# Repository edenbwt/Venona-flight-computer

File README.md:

# Venona flight computer
the goal of this flight computer is to be easy to manufacture be mobulable for all kind of mission 

## Goal

- log fly data
- 4 pyro chanel
- quite light
- Arduino C++ firmware

## Parts
- Teensy 3.6 dev board
- mpu6050
- bosch bmp280
- n chanel mosfet for pyro
- tricolor Led
- buzzer

## The rocket

- this is the rocket the computer will be tested on 
- this rocket is design on [Open Rocket](https://openrocket.info/)

## The board

- this is the board, i made it in one 10h go i probably fuck it up doing it BUT i think it will run for testing for now
- i will by all the part after christmas so i can try it out later in 2023
- this board is design on [Autodesk Eagle](http://eagle.autodesk.com/)

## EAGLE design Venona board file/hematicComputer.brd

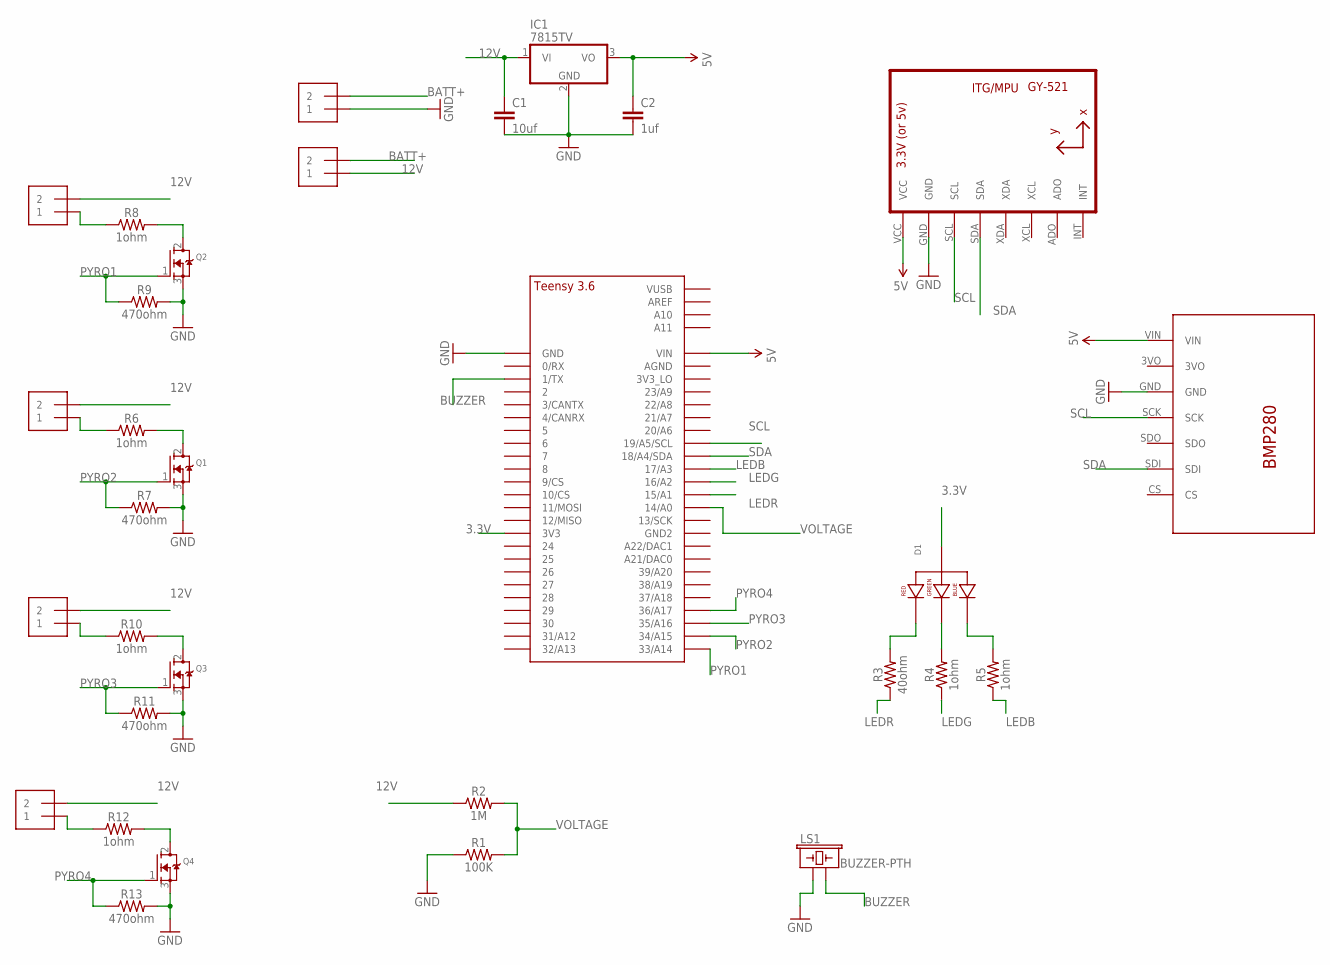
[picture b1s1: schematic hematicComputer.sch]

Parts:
C1: 10uf; CAP-PTH-2.54
C2: 1uf; CAP-PTH-2.54
D1: LED-RGB-CA-THRUCLEAR; LED-RGB-THRU
IC1: 7815TV; TO220V
J1, J2, J3, J4, J5, J6: 1X2-3.5MM
LS1: BUZZER-PTH; BUZZER-12MM
Q1, Q2, Q3, Q4: MOSFET-NGDS_TO220V; TO220V
R1: 100K; AXIAL-0.3
R2: 1M; AXIAL-0.3
R3: 40ohm; AXIAL-0.3
R4, R5, R6, R8, R10, R12: 1ohm; AXIAL-0.3
R7, R9, R11, R13: 470ohm; AXIAL-0.3
U1: GY-521MPU6050; GY-521
U$1: TEENSY_3.5/3.6_BASIC
U$2: BMP280

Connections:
3.3V: D1.2 (ANODE), U$1.3V3
5V: C2.1, IC1.3 (VO), U1.VCC, U$1.VIN, U$2.VIN
12V: C1.1, IC1.1 (VI), J2.1, J3.2, J4.2, J5.2, J6.2, R2.P$1 (1)
BATT+: J1.2, J2.2
BUZZER: LS1.- (2), U$1.1/TX
GND: C1.2, C2.2, IC1.2 (GND), J1.1, LS1.+ (1), Q1.3 (S), Q2.3 (S), Q3.3 (S), Q4.3 (S), R1.P$1 (1), R7.P$2 (2), R9.P$2 (2), R11.P$2 (2), R13.P$2 (2), U1.GND, U$1.GND, U$2.GND
LEDB: R5.P$1 (1), U$1.17/A3
LEDG: R4.P$1 (1), U$1.16/A2
LEDR: R3.P$1 (1), U$1.15/A1
unnamed: D1.1 (RED_CATHODE), R3.P$2 (2)
unnamed: D1.3 (GREEN_CATHODE), R4.P$2 (2)
unnamed: D1.4 (BLUE_CATHODE), R5.P$2 (2)
unnamed: Q1.2 (D), R6.P$2 (2)
unnamed: J6.1, R6.P$1 (1)
unnamed: J3.1, R8.P$1 (1)
unnamed: Q2.2 (D), R8.P$2 (2)
unnamed: J4.1, R10.P$1 (1)
unnamed: Q3.2 (D), R10.P$2 (2)
unnamed: J5.1, R12.P$1 (1)
unnamed: Q4.2 (D), R12.P$2 (2)
PYRO1: Q2.1 (G), R9.P$1 (1), U$1.33/A14
PYRO2: Q1.1 (G), R7.P$1 (1), U$1.34/A15
PYRO3: Q3.1 (G), R11.P$1 (1), U$1.35/A16
PYRO4: Q4.1 (G), R13.P$1 (1), U$1.36/A17
SCL: U1.SCL, U$1.19/A5/SCL, U$2.SCK
SDA: U1.SDA, U$1.18/A4/SDA, U$2.SDI
VOLTAGE: R1.P$2 (2), R2.P$2 (2), U$1.14/A0

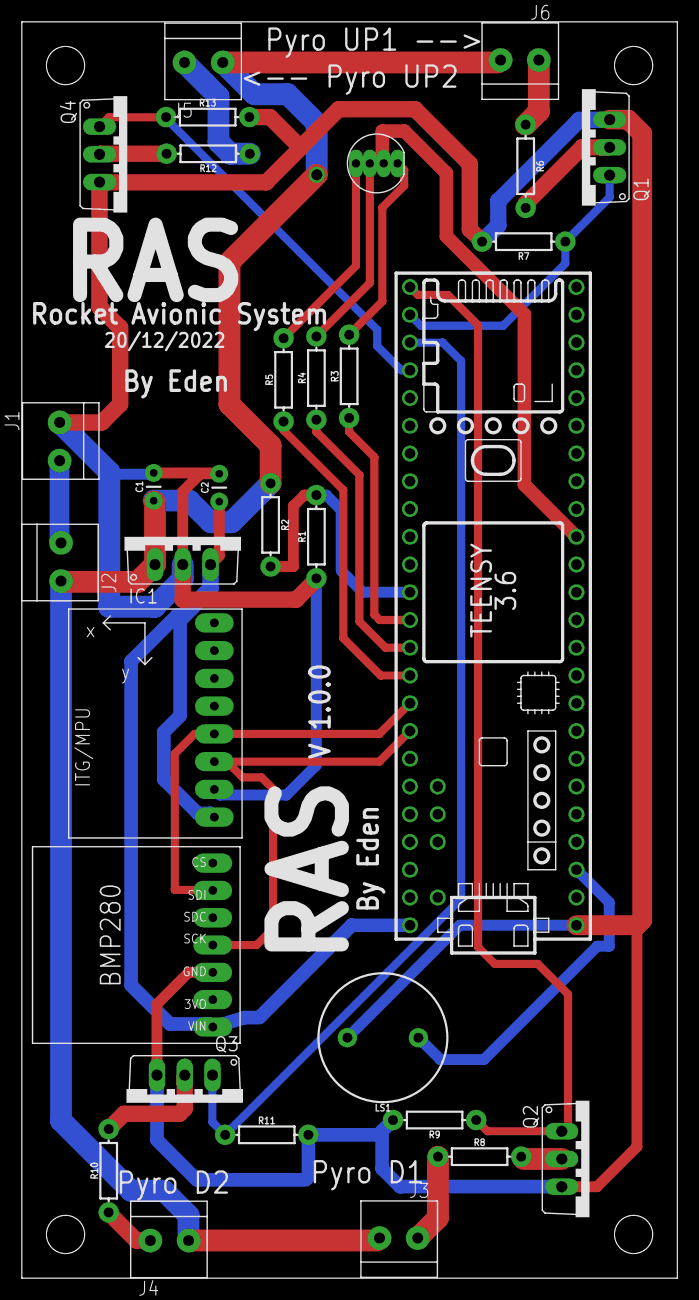
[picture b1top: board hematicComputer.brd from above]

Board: 2 copper layers, 60.0 x 115.0 mm, 31 parts (0 on the bottom side), 27 nets.

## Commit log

2023-01-05 Update main_code_for_fly_computer.ino
    add Led, buzzer and the part for rocket recovery
2023-01-08 Update main_code_for_fly_computer.ino
    added batterie % variable
2023-01-10 Update main_code_for_fly_computer.ino
    add futur fonction for sond of the rocket

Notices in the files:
parts and their libraries:
SparkFun-Capacitors: Licensing: Creative Commons ShareAlike 4.0 International - https://creativecommons.org/licenses/by-sa/4.0
SparkFun-LED: Licensing: CC v3.0 Share-Alike You are welcome to use this library for commercial purposes.
